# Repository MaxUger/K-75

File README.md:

# K-75
 75% Keyboard
 
 Front Side:

Back Side:

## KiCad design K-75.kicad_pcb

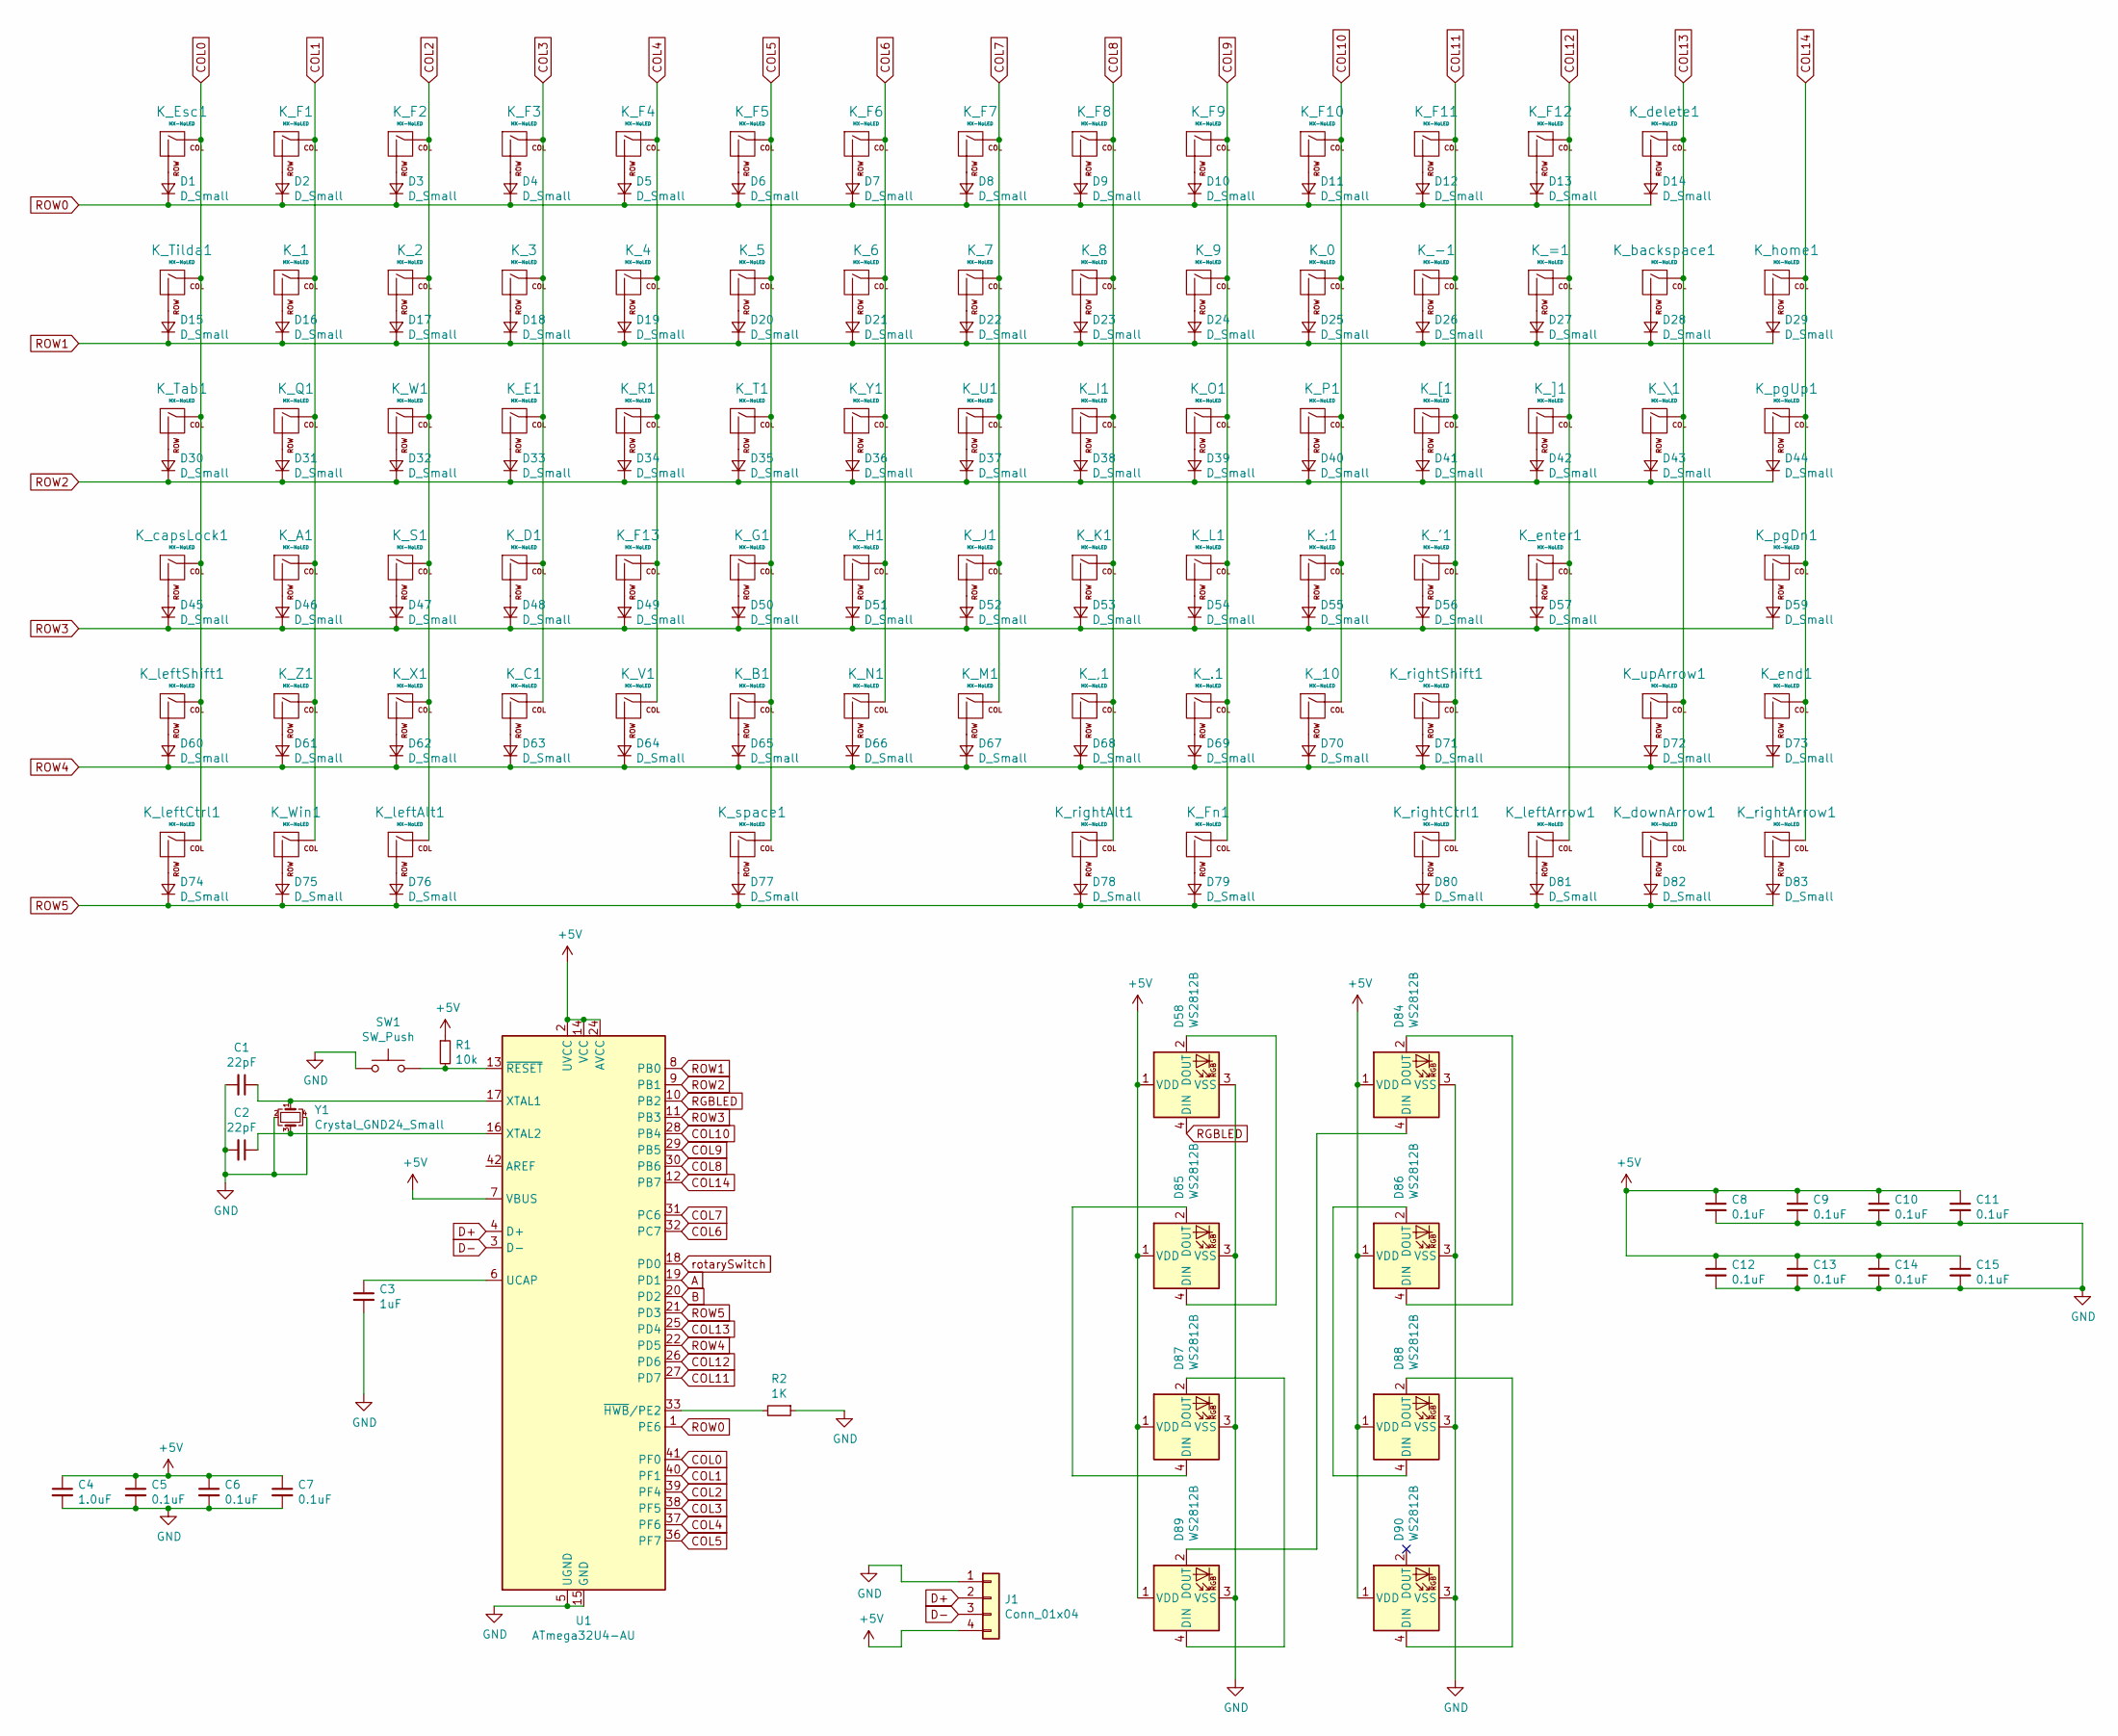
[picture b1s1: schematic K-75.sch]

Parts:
C1, C2: 22pF; C_0603_1608Metric
C3: 1uF; C_0603_1608Metric
C4: 1.0uF; C_0603_1608Metric
C5, C6, C7, C8, C9, C10, C11, C12, C13, C14, C15: 0.1uF; C_0603_1608Metric
D1, D2, D3, D4, D5, D6, D7, D8, D9, D10, D11, D12, D13, D14, D15, D16, D17, D18, D19, D20, D21, D22, D23, D24, D25, D26, D27, D28, D29, D30, D31, D32, D33, D34, D35, D36, D37, D38, D39, D40, D41, D42, D43, D44, D45, D46, D47, D48, D49, D50, D51, D52, D53, D54, D55, D56, D57, D59, D60, D61, D62, D63, D64, D65, D66, D67, D68, D69, D70, D71, D72, D73, D74, D75, D76, D77, D78, D79, D80, D81, D82, D83: D_Small; D_SOD-123
D58, D84, D85, D86, D87, D88, D89, D90: WS2812B; LED_WS2812B_PLCC4_5.0x5.0mm_P3.2mm
J1: Conn_01x04; JST-SR-4
K_0, K_1, K_2, K_3, K_4, K_5, K_6, K_7, K_8, K_9, K_10, K_.1: MX-NoLED; MXOnly-1U-Hotswap
K_'1: MX-NoLED; MXOnly-1U-Hotswap
K_,1: MX-NoLED; MXOnly-1U-Hotswap
K_-1: MX-NoLED; MXOnly-1U-Hotswap
K_;1: MX-NoLED; MXOnly-1U-Hotswap
K_=1: MX-NoLED; MXOnly-1U-Hotswap
K_A1: MX-NoLED; MXOnly-1U-Hotswap
K_B1: MX-NoLED; MXOnly-1U-Hotswap
K_C1: MX-NoLED; MXOnly-1U-Hotswap
K_D1: MX-NoLED; MXOnly-1U-Hotswap
K_E1: MX-NoLED; MXOnly-1U-Hotswap
K_Esc1: MX-NoLED; MXOnly-1U-Hotswap
K_F1, K_F2, K_F3, K_F4, K_F5, K_F6, K_F7, K_F8, K_F9, K_F10, K_F11, K_F12, K_F13: MX-NoLED; MXOnly-1U-Hotswap
K_Fn1: MX-NoLED; MXOnly-1U-Hotswap
K_G1: MX-NoLED; MXOnly-1U-Hotswap
K_H1: MX-NoLED; MXOnly-1U-Hotswap
K_I1: MX-NoLED; MXOnly-1U-Hotswap
K_J1: MX-NoLED; MXOnly-1U-Hotswap
K_K1: MX-NoLED; MXOnly-1U-Hotswap
K_L1: MX-NoLED; MXOnly-1U-Hotswap
K_M1: MX-NoLED; MXOnly-1U-Hotswap
K_N1: MX-NoLED; MXOnly-1U-Hotswap
K_O1: MX-NoLED; MXOnly-1U-Hotswap
K_P1: MX-NoLED; MXOnly-1U-Hotswap
K_Q1: MX-NoLED; MXOnly-1U-Hotswap
K_R1: MX-NoLED; MXOnly-1U-Hotswap
K_S1: MX-NoLED; MXOnly-1U-Hotswap
K_T1: MX-NoLED; MXOnly-1U-Hotswap
K_Tab1: MX-NoLED; MXOnly-1.5U-Hotswap
K_Tilda1: MX-NoLED; MXOnly-1U-Hotswap
K_U1: MX-NoLED; MXOnly-1U-Hotswap
K_V1: MX-NoLED; MXOnly-1U-Hotswap
K_W1: MX-NoLED; MXOnly-1U-Hotswap
K_Win1: MX-NoLED; MXOnly-1.25U-Hotswap
K_X1: MX-NoLED; MXOnly-1U-Hotswap
K_Y1: MX-NoLED; MXOnly-1U-Hotswap
K_Z1: MX-NoLED; MXOnly-1U-Hotswap
K_[1: MX-NoLED; MXOnly-1U-Hotswap
K_\1: MX-NoLED; MXOnly-1U-Hotswap
K_]1: MX-NoLED; MXOnly-1U-Hotswap
K_backspace1: MX-NoLED; MXOnly-2U-Hotswap
K_capsLock1: MX-NoLED; MXOnly-1.75U-Hotswap
K_delete1: MX-NoLED; MXOnly-1U-Hotswap
K_downArrow1: MX-NoLED; MXOnly-1U-Hotswap
K_end1: MX-NoLED; MXOnly-1U-Hotswap
K_enter1: MX-NoLED; MXOnly-2.25U-Hotswap
K_home1: MX-NoLED; MXOnly-1U-Hotswap
K_leftAlt1: MX-NoLED; MXOnly-1.25U-Hotswap
K_leftArrow1: MX-NoLED; MXOnly-1U-Hotswap
K_leftCtrl1: MX-NoLED; MXOnly-1.25U-Hotswap
K_leftShift1: MX-NoLED; MXOnly-2.25U-Hotswap
K_pgDn1: MX-NoLED; MXOnly-1U-Hotswap
K_pgUp1: MX-NoLED; MXOnly-1U-Hotswap
K_rightAlt1: MX-NoLED; MXOnly-1U-Hotswap
K_rightArrow1: MX-NoLED; MXOnly-1U-Hotswap
K_rightCtrl1: MX-NoLED; MXOnly-1U-Hotswap
K_rightShift1: MX-NoLED; MXOnly-1.75U-Hotswap
K_space1: MX-NoLED; MXOnly-6.25U-Hotswap
K_upArrow1: MX-NoLED; MXOnly-1U-Hotswap
R1: 10k; R_0805_2012Metric
R2: 1K; R_0805_2012Metric
SW1: SW_Push; SKQG-1155865
U1: ATmega32U4-AU; TQFP-44_10x10mm_P0.8mm
Y1: Crystal_GND24_Small; Crystal_SMD_3225-4Pin_3.2x2.5mm

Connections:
+5V: C4.1, C5.1, C6.1, C7.1, C8.1, C9.1, C10.1, C11.1, C12.1, C13.1, C14.1, C15.1, D58.1 (VDD), D84.1 (VDD), D85.1 (VDD), D86.1 (VDD), D87.1 (VDD), D88.1 (VDD), D89.1 (VDD), D90.1 (VDD), J1.4, R1.1, U1.2 (UVCC), U1.7 (VBUS), U1.14 (VCC), U1.24 (AVCC), U1.34 (VCC), U1.44 (AVCC)
COL0: K_Esc1.1 (COL), K_Tab1.1 (COL), K_Tilda1.1 (COL), K_capsLock1.1 (COL), K_leftCtrl1.1 (COL), K_leftShift1.1 (COL), U1.41 (PF0)
COL1: K_1.1 (COL), K_A1.1 (COL), K_F1.1 (COL), K_Q1.1 (COL), K_Win1.1 (COL), K_Z1.1 (COL), U1.40 (PF1)
COL2: K_2.1 (COL), K_F2.1 (COL), K_S1.1 (COL), K_W1.1 (COL), K_X1.1 (COL), K_leftAlt1.1 (COL), U1.39 (PF4)
COL3: K_3.1 (COL), K_C1.1 (COL), K_D1.1 (COL), K_E1.1 (COL), K_F3.1 (COL), U1.38 (PF5)
COL4: K_4.1 (COL), K_F4.1 (COL), K_F13.1 (COL), K_R1.1 (COL), K_V1.1 (COL), U1.37 (PF6)
COL5: K_5.1 (COL), K_B1.1 (COL), K_F5.1 (COL), K_G1.1 (COL), K_T1.1 (COL), K_space1.1 (COL), U1.36 (PF7)
COL6: K_6.1 (COL), K_F6.1 (COL), K_H1.1 (COL), K_N1.1 (COL), K_Y1.1 (COL), U1.32 (PC7)
COL7: K_7.1 (COL), K_F7.1 (COL), K_J1.1 (COL), K_M1.1 (COL), K_U1.1 (COL), U1.31 (PC6)
COL8: K_8.1 (COL), K_,1.1 (COL), K_F8.1 (COL), K_I1.1 (COL), K_K1.1 (COL), K_rightAlt1.1 (COL), U1.30 (PB6)
COL9: K_9.1 (COL), K_.1.1 (COL), K_F9.1 (COL), K_Fn1.1 (COL), K_L1.1 (COL), K_O1.1 (COL), U1.29 (PB5)
COL10: K_0.1 (COL), K_10.1 (COL), K_;1.1 (COL), K_F10.1 (COL), K_P1.1 (COL), U1.28 (PB4)
COL11: K_'1.1 (COL), K_-1.1 (COL), K_F11.1 (COL), K_[1.1 (COL), K_rightCtrl1.1 (COL), K_rightShift1.1 (COL), U1.27 (PD7)
COL12: K_=1.1 (COL), K_F12.1 (COL), K_]1.1 (COL), K_enter1.1 (COL), K_leftArrow1.1 (COL), U1.26 (PD6)
COL13: K_\1.1 (COL), K_backspace1.1 (COL), K_delete1.1 (COL), K_downArrow1.1 (COL), K_upArrow1.1 (COL), U1.25 (PD4)
COL14: K_end1.1 (COL), K_home1.1 (COL), K_pgDn1.1 (COL), K_pgUp1.1 (COL), K_rightArrow1.1 (COL), U1.12 (PB7)
D+: J1.2, U1.4 (D+)
D-: J1.3, U1.3 (D-)
GND: C1.2, C2.2, C3.2, C4.2, C5.2, C6.2, C7.2, C8.2, C9.2, C10.2, C11.2, C12.2, C13.2, C14.2, C15.2, D58.3 (VSS), D84.3 (VSS), D85.3 (VSS), D86.3 (VSS), D87.3 (VSS), D88.3 (VSS), D89.3 (VSS), D90.3 (VSS), J1.1, R2.1, SW1.1, U1.5 (UGND), U1.15 (GND), U1.23 (GND), U1.35 (GND), U1.43 (GND), Y1.2, Y1.4
unnamed: C1.1, U1.17 (XTAL1), Y1.1
unnamed: C2.1, U1.16 (XTAL2), Y1.3
unnamed: C3.1, U1.6 (UCAP)
unnamed: D1.2 (A), K_Esc1.2 (ROW)
unnamed: D2.2 (A), K_F1.2 (ROW)
unnamed: D3.2 (A), K_F2.2 (ROW)
unnamed: D4.2 (A), K_F3.2 (ROW)
unnamed: D5.2 (A), K_F4.2 (ROW)
unnamed: D6.2 (A), K_F5.2 (ROW)
unnamed: D7.2 (A), K_F6.2 (ROW)
unnamed: D8.2 (A), K_F7.2 (ROW)
unnamed: D9.2 (A), K_F8.2 (ROW)
unnamed: D10.2 (A), K_F9.2 (ROW)
unnamed: D11.2 (A), K_F10.2 (ROW)
unnamed: D12.2 (A), K_F11.2 (ROW)
unnamed: D13.2 (A), K_F12.2 (ROW)
unnamed: D14.2 (A), K_delete1.2 (ROW)
unnamed: D15.2 (A), K_Tilda1.2 (ROW)
unnamed: D16.2 (A), K_1.2 (ROW)
unnamed: D17.2 (A), K_2.2 (ROW)
unnamed: D18.2 (A), K_3.2 (ROW)
unnamed: D19.2 (A), K_4.2 (ROW)
unnamed: D20.2 (A), K_5.2 (ROW)
unnamed: D21.2 (A), K_6.2 (ROW)
unnamed: D22.2 (A), K_7.2 (ROW)
unnamed: D23.2 (A), K_8.2 (ROW)
unnamed: D24.2 (A), K_9.2 (ROW)
unnamed: D25.2 (A), K_0.2 (ROW)
unnamed: D26.2 (A), K_-1.2 (ROW)
unnamed: D27.2 (A), K_=1.2 (ROW)
unnamed: D28.2 (A), K_backspace1.2 (ROW)
unnamed: D29.2 (A), K_home1.2 (ROW)
unnamed: D30.2 (A), K_Tab1.2 (ROW)
unnamed: D31.2 (A), K_Q1.2 (ROW)
unnamed: D32.2 (A), K_W1.2 (ROW)
unnamed: D33.2 (A), K_E1.2 (ROW)
unnamed: D34.2 (A), K_R1.2 (ROW)
unnamed: D35.2 (A), K_T1.2 (ROW)
unnamed: D36.2 (A), K_Y1.2 (ROW)
unnamed: D37.2 (A), K_U1.2 (ROW)
unnamed: D38.2 (A), K_I1.2 (ROW)
unnamed: D39.2 (A), K_O1.2 (ROW)
unnamed: D40.2 (A), K_P1.2 (ROW)
unnamed: D41.2 (A), K_[1.2 (ROW)
unnamed: D42.2 (A), K_]1.2 (ROW)
unnamed: D43.2 (A), K_\1.2 (ROW)
unnamed: D44.2 (A), K_pgUp1.2 (ROW)
unnamed: D45.2 (A), K_capsLock1.2 (ROW)
unnamed: D46.2 (A), K_A1.2 (ROW)
unnamed: D47.2 (A), K_S1.2 (ROW)
unnamed: D48.2 (A), K_D1.2 (ROW)
unnamed: D49.2 (A), K_F13.2 (ROW)
unnamed: D50.2 (A), K_G1.2 (ROW)
unnamed: D51.2 (A), K_H1.2 (ROW)
unnamed: D52.2 (A), K_J1.2 (ROW)
unnamed: D53.2 (A), K_K1.2 (ROW)
unnamed: D54.2 (A), K_L1.2 (ROW)
unnamed: D55.2 (A), K_;1.2 (ROW)
unnamed: D56.2 (A), K_'1.2 (ROW)
unnamed: D57.2 (A), K_enter1.2 (ROW)
unnamed: D58.2 (DOUT), D85.4 (DIN)
unnamed: D59.2 (A), K_pgDn1.2 (ROW)
unnamed: D60.2 (A), K_leftShift1.2 (ROW)
unnamed: D61.2 (A), K_Z1.2 (ROW)
unnamed: D62.2 (A), K_X1.2 (ROW)
unnamed: D63.2 (A), K_C1.2 (ROW)
unnamed: D64.2 (A), K_V1.2 (ROW)
unnamed: D65.2 (A), K_B1.2 (ROW)
unnamed: D66.2 (A), K_N1.2 (ROW)
unnamed: D67.2 (A), K_M1.2 (ROW)
unnamed: D68.2 (A), K_,1.2 (ROW)
unnamed: D69.2 (A), K_.1.2 (ROW)
unnamed: D70.2 (A), K_10.2 (ROW)
unnamed: D71.2 (A), K_rightShift1.2 (ROW)
unnamed: D72.2 (A), K_upArrow1.2 (ROW)
unnamed: D73.2 (A), K_end1.2 (ROW)
unnamed: D74.2 (A), K_leftCtrl1.2 (ROW)
unnamed: D75.2 (A), K_Win1.2 (ROW)
unnamed: D76.2 (A), K_leftAlt1.2 (ROW)
unnamed: D77.2 (A), K_space1.2 (ROW)
unnamed: D78.2 (A), K_rightAlt1.2 (ROW)
unnamed: D79.2 (A), K_Fn1.2 (ROW)
unnamed: D80.2 (A), K_rightCtrl1.2 (ROW)
unnamed: D81.2 (A), K_leftArrow1.2 (ROW)
unnamed: D82.2 (A), K_downArrow1.2 (ROW)
unnamed: D83.2 (A), K_rightArrow1.2 (ROW)
unnamed: D84.2 (DOUT), D86.4 (DIN)
unnamed: D84.4 (DIN), D89.2 (DOUT)
unnamed: D85.2 (DOUT), D87.4 (DIN)
unnamed: D86.2 (DOUT), D88.4 (DIN)
unnamed: D87.2 (DOUT), D89.4 (DIN)
unnamed: D88.2 (DOUT), D90.4 (DIN)
unnamed: R1.2, SW1.2, U1.13 (~RESET)
unnamed: R2.2, U1.33 (~HWB~/PE2)
RGBLED: D58.4 (DIN), U1.10 (PB2)
ROW0: D1.1 (K), D2.1 (K), D3.1 (K), D4.1 (K), D5.1 (K), D6.1 (K), D7.1 (K), D8.1 (K), D9.1 (K), D10.1 (K), D11.1 (K), D12.1 (K), D13.1 (K), D14.1 (K), U1.1 (PE6)
ROW1: D15.1 (K), D16.1 (K), D17.1 (K), D18.1 (K), D19.1 (K), D20.1 (K), D21.1 (K), D22.1 (K), D23.1 (K), D24.1 (K), D25.1 (K), D26.1 (K), D27.1 (K), D28.1 (K), D29.1 (K), U1.8 (PB0)
ROW2: D30.1 (K), D31.1 (K), D32.1 (K), D33.1 (K), D34.1 (K), D35.1 (K), D36.1 (K), D37.1 (K), D38.1 (K), D39.1 (K), D40.1 (K), D41.1 (K), D42.1 (K), D43.1 (K), D44.1 (K), U1.9 (PB1)
ROW3: D45.1 (K), D46.1 (K), D47.1 (K), D48.1 (K), D49.1 (K), D50.1 (K), D51.1 (K), D52.1 (K), D53.1 (K), D54.1 (K), D55.1 (K), D56.1 (K), D57.1 (K), D59.1 (K), U1.11 (PB3)
ROW4: D60.1 (K), D61.1 (K), D62.1 (K), D63.1 (K), D64.1 (K), D65.1 (K), D66.1 (K), D67.1 (K), D68.1 (K), D69.1 (K), D70.1 (K), D71.1 (K), D72.1 (K), D73.1 (K), U1.22 (PD5)
ROW5: D74.1 (K), D75.1 (K), D76.1 (K), D77.1 (K), D78.1 (K), D79.1 (K), D80.1 (K), D81.1 (K), D82.1 (K), D83.1 (K), U1.21 (PD3)

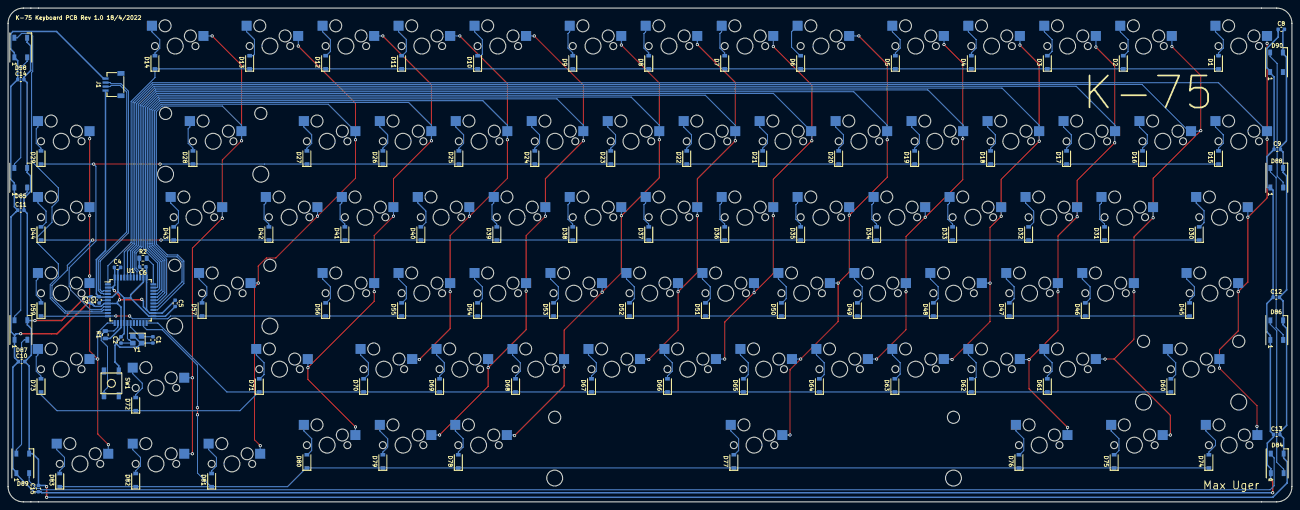
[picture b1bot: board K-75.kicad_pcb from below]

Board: 2 copper layers, 321.9 x 123.8 mm, 193 parts (111 on the bottom side), 120 nets.

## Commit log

2022-03-14 Added submodules
2022-03-14 Finished MCU schematic
2022-03-14 Finished key matrix
2022-03-14 Added USB connector
2022-03-14 Assigned footprints
2022-03-15 Board setup
2022-03-16 Key placements
2022-03-16 Key placement
2022-03-16 Finished key placement with 3d models
2022-03-16 Finished diode placement
2022-03-17 Edge cuts
2022-03-21 Finished diode matrix
2022-03-22 Finished vertical matrix trace routing
2022-04-18 Tracing progress
2022-04-18 Improved routing
2022-04-19 Added LEDs
2022-04-19 Finished routing
2022-04-19 Added USB traces
2022-04-19 Finished traces
2022-04-20 Fabrication outputs
